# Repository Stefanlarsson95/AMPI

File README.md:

The AMPI Project
=============

##### Base on:
https://github.com/usul27/hifiberry-dsp

https://github.com/diehardsk/Volumio-OledUI

## Scrips

#### Configure DPS
Run command:
````bash
./AMPI/push_config.sh
````

#### Check voltage
Power status: 0x50005 =  bad, 0x50000 = good
````bash
sudo vcgencmd get_throttled	
````

#### RPI Core temp
The CPU core temp can be printed by the bash script:
````bash
~/AMPI/RpiTemp.sh
 ````

#### RPI AMP temp
The Amplifier heatsink temperature can med printed by the bash script:
````bash
~/AMPI/ampTemp.sh
 ````

## Instalation

#### installation steps
```bash
sudo apt update && sudo apt upgrade
sudo apt install -y python3-dev python3-pip libfreetype6-dev libjpeg-dev build-essential python3-rpi.gpio libatlas-base-dev
sudo pip3 install setuptools pip wheel
sudo pip3 install numpy
sudo pip3 install --upgrade socketIO-client3
sudo -H pip3 install --upgrade luma.oled
git clone https://github.com/Stefanlarsson95/AMPI
chmod +x ~/AMPI/AMPI.py ~/AMPI/push_config.sh ~/AMPI/RpiTemp.sh ~/AMPI/ampTemp.sh
sudo cp ~/AMPI/ampi.service /lib/systemd/system/
sudo cp ~/AMPI/dsp_config.service /lib/systemd/system/
sudo systemctl daemon-reload
sudo systemctl enable ampi.service
sudo systemctl enable dsp_config.service
```

 To enable the Oled display, SPI communication need to be enabled in the /boot/config.txt file.
 Add the following line.
 
 ```shell script
dtparam=spi=on
 ```
 
## ADAU1701 Installation
 Based on the guide and overlay from [digital-audio-labs.jimdofree.com](https://digital-audio-labs.jimdofree.com/english/raspberry-pi/adau1701-i2s-driver/)
 
 Big thanks to [MKSounds](https://github.com/MKSounds)!

Step1: Get overlay and copy to overlays folder
```bash
 git clone https://github.com/MKSounds/ADAU1701-I2S-Audio-Driver-for-Raspberry-Pi.git
```

Step2: Add overlay to overlay folder
```
sudo cp ADAU1701-I2S-Audio-Driver-for-Raspberry-Pi/adau1701-i2s.dtbo /boot/overlays
```
Step3: Add ADAU1701 to Volumio soundcards
Open soundcard JSON
```
sudo cp ADAU1701-I2S-Audio-Driver-for-Raspberry-Pi/adau1701-i2s.dtbo /boot/overlays
```
add ADAU1701 soundcard:
```
{"id":"adau1701-i2s","name":"ADAU1701 I2S Output","overlay":"adau1701-i2s","alsanum":"1","mixer":"Digital","modules":"","script":"","needsreboot":"yes"},
```
OBS: replace "Digital" with "" if Hardware volume is not used!

Step4: add dummy mixer to enable Hardware Volume

```shell script
state.Output {
	control.1 {
		iface MIXER
		name ADAU1701
		value.0 99
		value.1 99
		comment {
			access 'read write user'
			type INTEGER
			count 2
			range '0 - 99'
			tlv '00000001000000080000000000000032'
			dbmin 0
			dbmax 4950
			dbvalue.0 4950
			dbvalue.1 4950
		}
	}
}
```

 Finally reboot system
 
 ```bash
 reboot
 ```

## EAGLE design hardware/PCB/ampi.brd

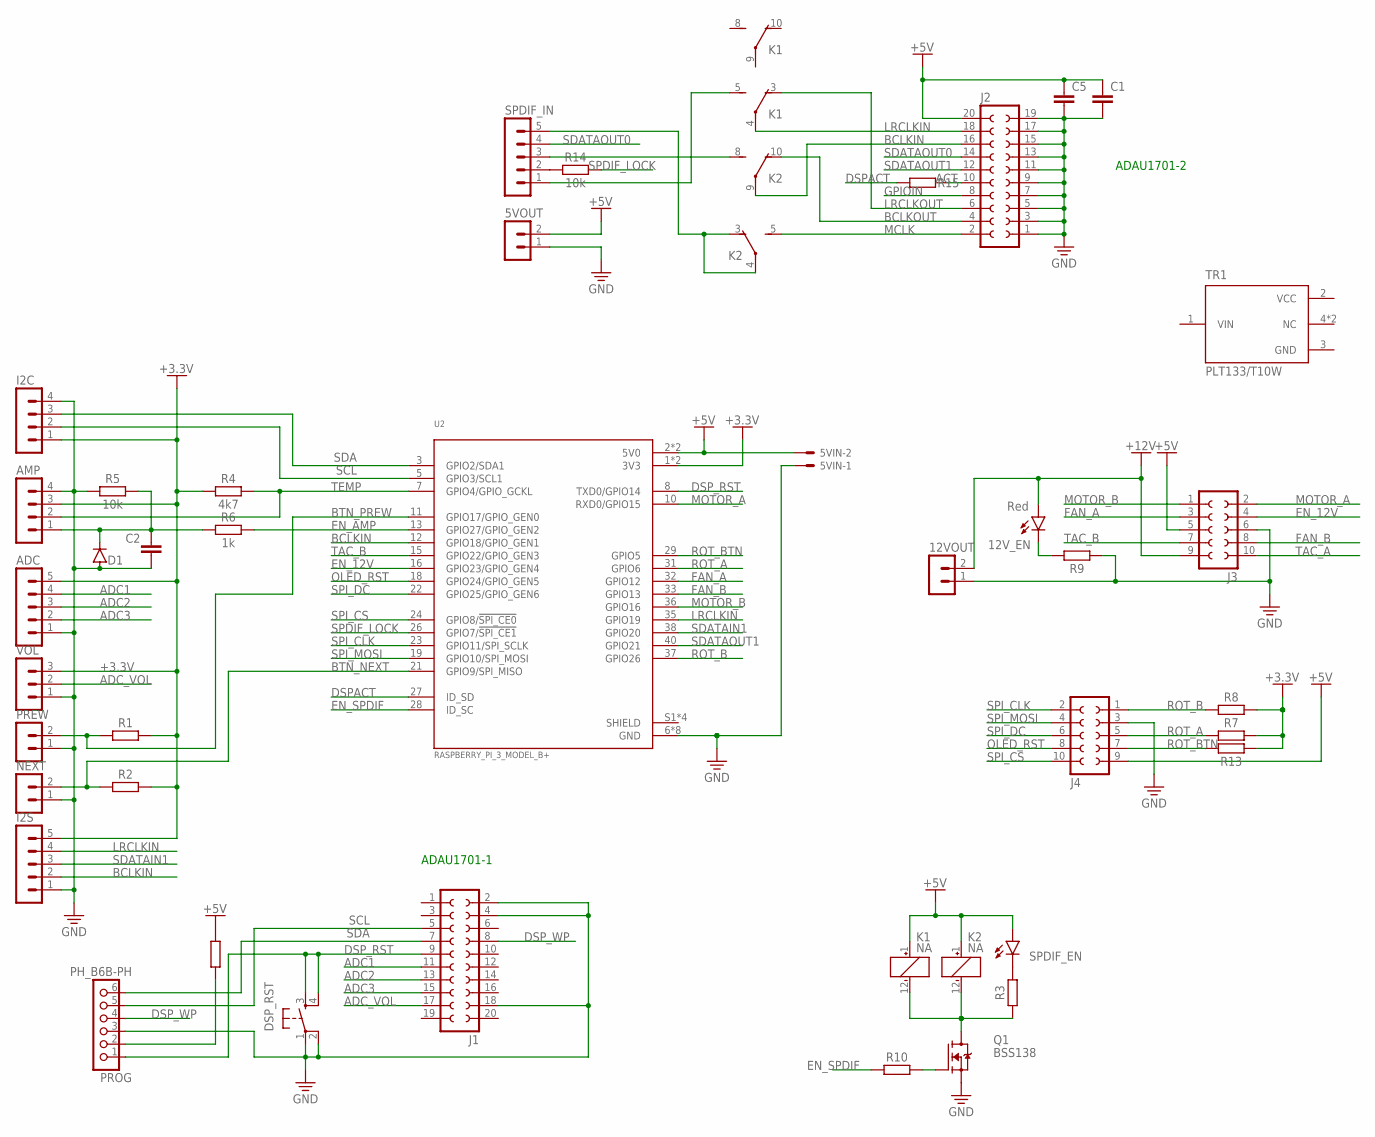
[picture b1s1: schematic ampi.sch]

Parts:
5VIN: JST-XH-02-PIN-LONG-PAD; JST-XH-02-PACKAGE-LONG-PAD
5VOUT, 12VOUT: S2B-EH
12V_EN: Red; CHIP-LED0805
ADC: S5B-EH
AMP: S4B-EH
C1: C7.5/4; C7.5B4
C2: C_CHIP-0603(1608-METRIC); CAPC1608X85
C5: C-EUC0805K; C0805K
D1: CGRM4001-G; SOD-123_MINI-SMA
DSP_RST: DTS-6
I2C: S4B-EH
I2S: S5B-EH
J1, J2: SOCKET-20V; S20V
J3, J4: SOCKET-10V; S10V
K1, K2: NA
NEXT: S2B-EH
PREW: S2B-EH
PROG: PH_B6B-PH; B6B-PH
Q1: BSS138; SOT23
R1, R2, R3, R7, R8, R9, R10, R13, R15: R_CHIP-0603(1608-METRIC); RESC1608X60
R4: 4k7; RESC1608X60
R5, R14: 10k; RESC1608X60
R6: 1k; RESC1608X60
R12: R_CHIP-0402(1005-METRIC); RESC1005X40
SPDIF_EN: LEDCHIP-LED0805; CHIP-LED0805
SPDIF_IN: S5B-EH
TR1: PLT133/T10W; XDCR_PLT133/T10W
U2: RASPBERRY_PI_3_MODEL_B+; MODULE_RASPBERRY_PI_3_MODEL_B+
VOL: S3B-EH

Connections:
+3.3V: ADC.5, AMP.3, I2C.1, I2S.5, R1.2, R2.2, R4.1, R7.2, R8.2, R13.2, U2.1 (3V3), U2.17 (3V3), VOL.3
+5V: 5VIN.2, 5VOUT.2, C1.1, C5.1, J2.20, J3.5, J4.9, K1.1 (+), K2.1 (+), R12.2, SPDIF_EN.A, U2.2 (5V0), U2.4 (5V0)
+12V: 12VOUT.2, 12V_EN.A, J3.9
ACT: J2.10, R15.2
ADC1: ADC.4, J1.11
ADC2: ADC.3, J1.13
ADC3: ADC.2, J1.15
ADC_VOL: J1.17, VOL.2
BCLKIN: I2S.2, J2.16, K2.9, U2.12 (GPIO18/GPIO_GEN1)
BCLKOUT: J2.4, K2.10 (O)
BTN_NEXT: NEXT.2, R2.1, U2.21 (GPIO9/SPI_MISO)
BTN_PREW: PREW.2, R1.1, U2.11 (GPIO17/GPIO_GEN0)
DSPACT: R15.1, U2.27 (ID_SD)
DSP_RST: DSP_RST.3, DSP_RST.4, J1.9, PROG.1, U2.8 (TXD0/GPIO14)
DSP_WP: J1.8, PROG.4
EN_12V: J3.4, U2.16 (GPIO23/GPIO_GEN4)
EN_AMP: R6.2, U2.13 (GPIO27/GPIO_GEN2)
EN_SPDIF: R10.1, U2.28 (ID_SC)
FAN_A: J3.3, U2.32 (GPIO12)
FAN_B: J3.8, U2.33 (GPIO13)
GND: 5VIN.1, 5VOUT.1, 12VOUT.1, ADC.1, AMP.4, C1.2, C2.2, C5.2, D1.A, DSP_RST.1, DSP_RST.2, I2C.4, I2S.1, J1.2, J1.4, J1.18, J2.1, J2.3, J2.5, J2.7, J2.9, J2.11, J2.13, J2.15, J2.17, J2.19, J3.6, J4.3, NEXT.1, PREW.1, PROG.3, Q1.2 (S), R5.1, R9.2, TR1.3 (GND), U2.6 (GND), U2.9 (GND), U2.14 (GND), U2.20 (GND), U2.25 (GND), U2.30 (GND), U2.34 (GND), U2.39 (GND), VOL.1
GPIOIN: J2.8
LRCLKIN: I2S.4, J2.18, K1.4, U2.35 (GPIO19)
LRCLKOUT: J2.6, K1.3 (O)
MCLK: J2.2, K2.5 (S)
MOTOR_A: J3.2, U2.10 (RXD0/GPIO15)
MOTOR_B: J3.1, U2.36 (GPIO16)
unnamed: R3.2, SPDIF_EN.C
unnamed: K1.12 (-), K2.12 (-), Q1.3 (D), R3.1
unnamed: R14.1, SPDIF_IN.2
unnamed: 12V_EN.C, R9.1
unnamed: Q1.1 (G), R10.2
unnamed: K2.8 (S), SPDIF_IN.3
unnamed: K2.3 (O), K2.4, SPDIF_IN.5
unnamed: PROG.2, R12.1
unnamed: K1.5 (S), SPDIF_IN.1
unnamed: AMP.1, C2.1, D1.C, R5.2, R6.1
OLED_RST: J4.8, U2.18 (GPIO24/GPIO_GEN5)
ROT_A: J4.5, R7.1, U2.31 (GPIO6)
ROT_B: J4.1, R8.1, U2.37 (GPIO26)
ROT_BTN: J4.7, R13.1, U2.29 (GPIO5)
SCL: I2C.2, J1.5, PROG.5, U2.5 (GPIO3/SCL1)
SDA: I2C.3, J1.7, PROG.6, U2.3 (GPIO2/SDA1)
SDATAIN1: I2S.3, U2.38 (GPIO20)
SDATAOUT0: J2.14, SPDIF_IN.4
SDATAOUT1: J2.12, U2.40 (GPIO21)
SHIELD: U2.S1 (SHIELD), U2.S2 (SHIELD), U2.S3 (SHIELD), U2.S4 (SHIELD)
SPDIF_LOCK: R14.2, U2.26 (GPIO7/!SPI_CE1!)
SPI_CLK: J4.2, U2.23 (GPIO11/SPI_SCLK)
SPI_CS: J4.10, U2.24 (GPIO8/!SPI_CE0!)
SPI_DC: J4.6, U2.22 (GPIO25/GPIO_GEN6)
SPI_MOSI: J4.4, U2.19 (GPIO10/SPI_MOSI)
TAC_A: J3.10
TAC_B: J3.7, U2.15 (GPIO22/GPIO_GEN3)
TEMP: AMP.2, R4.2, U2.7 (GPIO4/GPIO_GCKL)
VCC: TR1.2 (VCC)

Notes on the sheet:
ADAU1701-1
ADAU1701-2

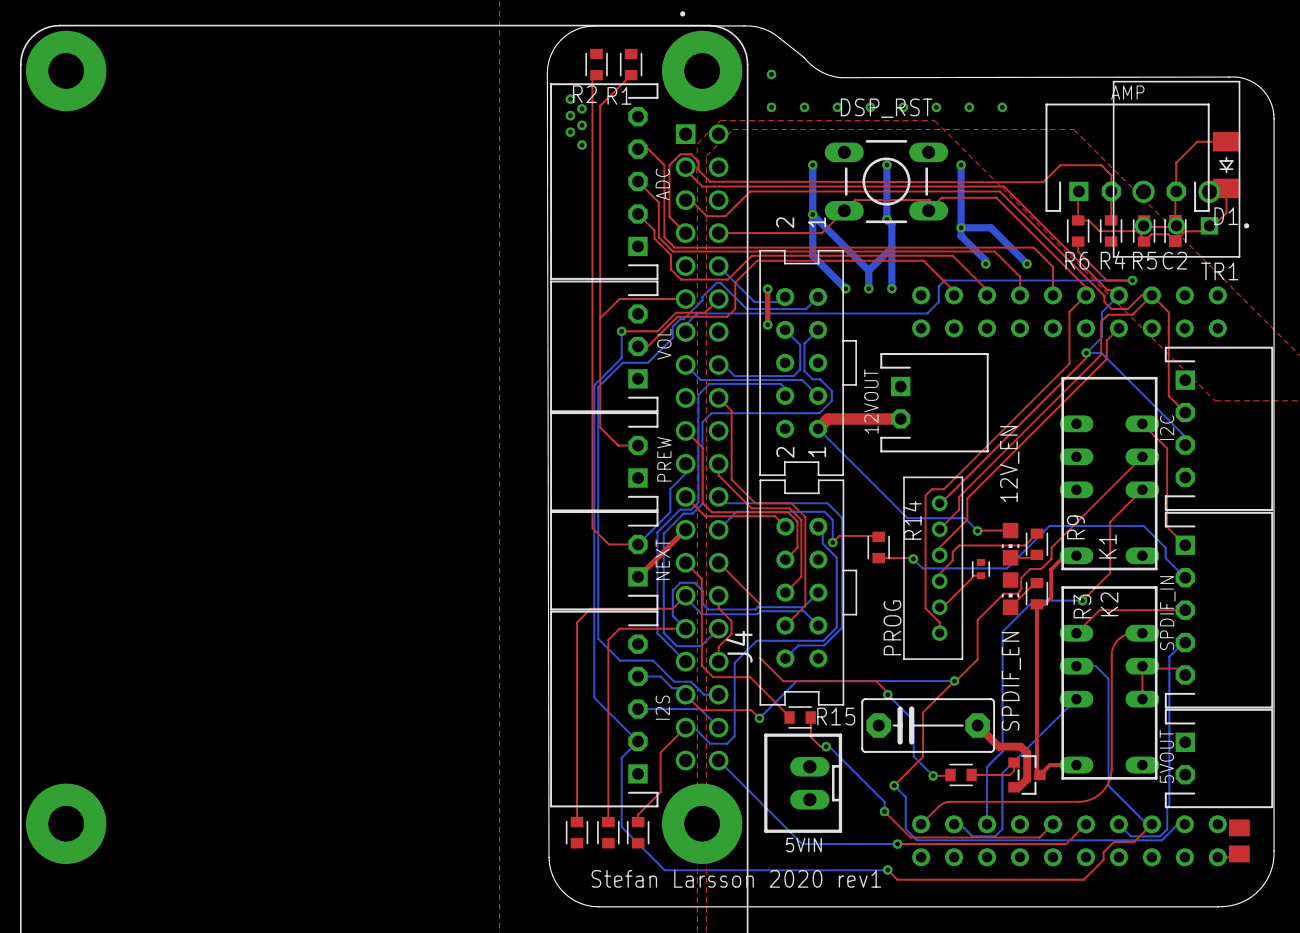
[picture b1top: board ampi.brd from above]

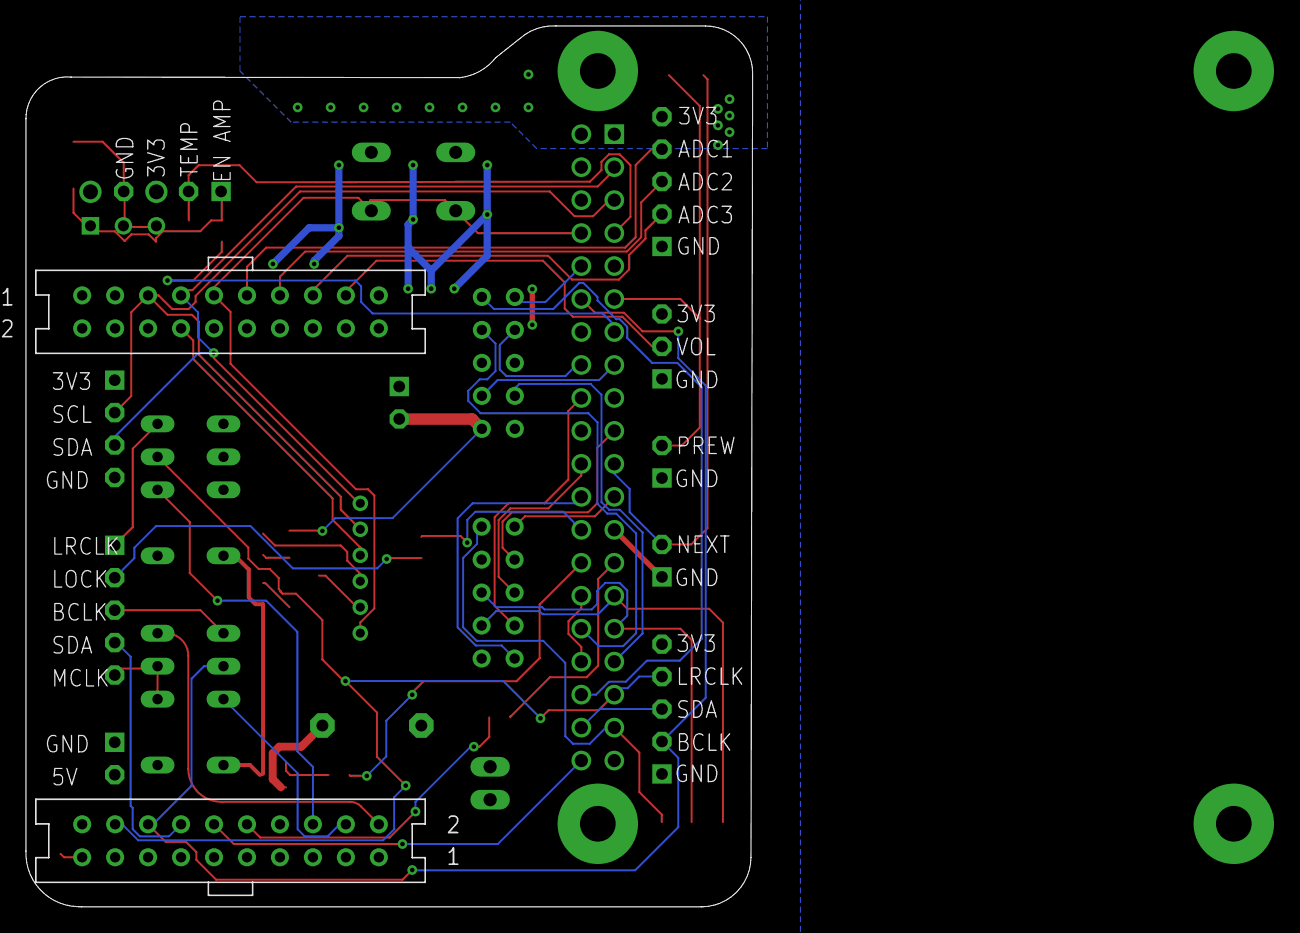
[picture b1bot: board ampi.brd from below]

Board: 2 copper layers, 56.0 x 67.9 mm, 42 parts (2 on the bottom side), 53 nets.

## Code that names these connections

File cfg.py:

import RPi.GPIO as GPIO
import modules.dsp_register as dsp_reg
import pathlib
from luma.core.interface.serial import spi
from luma.oled.device import ssd1322
from modules.logger import *
from hardware import sigmaimporter
from threading import Lock, Event

# Setup
log = Log()
_path = str(pathlib.Path().absolute())
_root_path = _path.rsplit('/', 1)[0]
i2c_lock = Lock()
volume_event = Event()  # todo implement or remove
eq_event = Event()  # todo implement or remove

"""
General
"""
amp_always_off = False
emit_volume = False
emit_track = False
emit_shutdown = False
standby = False
mute = False
log.set_level(LOGLEVEL.INFO)

"""
Temp control
"""
AMP_TEMP_TARGET = 60
CPU_TEMP_TARGET = 60
CHASSIS_FAN_MAX_RPM = 5000
AMP_FAN_MAX_RPM = 4500

"""
Sources
"""
RPI_ENABLED = True
AUX_ENABLED = True
SPDIF_ENABLED = False
SOURCE_AUX = 0
SOURCE_RPI = 1
SOURCE_SPDIF = 2
SOURCE_AUTO = 3
INIT_SOURCE = None  # will read default from DSP
volumio_source = INIT_SOURCE

"""
GPIO config
"""
# Setup Mutual action pins
# pwr12v = POWER12V()

# Input
ACTIVITY_PIN = 0
ROT_ENTER_PIN = 5
ROT_A_PIN = 6
SPDIF_LOCK_PIN = 7
BTN_PREV = 17
BTN_NEXT = 9
AMPLIFIER_FAN_TACH_PIN = None
CHASSIS_FAN_TACH_PIN = 22
ROT_B_PIN = IR_PIN = 26
LRCLK_PIN = 19

# Output
SPDIF_ENABLE_PIN = 1
DSP_RST_PIN = 14
VOL_UP_PIN = 15
VOL_DN_PIN = 16
CHASSIS_FAN_PIN = 12
AMPLIFIER_FAN_PIN = 13
PWR_EN_12V_PIN = 23
AMP_EN_PIN = 27

"""
OlED/UI
"""
VOLUMIO_HOST = volumio_host = 'localhost'
VOLUMIO_PORT = volumio_port = 3000
VOLUME_DT = 5  # volume adjustment step

UPDATE_INTERVAL = 1 / 15  # 1/fps
STANDBY_UPDATE_INTERVAL = 1
PIXEL_SHIFT_TIME = 120  # time between picture position shifts in sec.

# todo merge to state class usage
STATE_NONE = -1
STATE_PLAYER = 0
STATE_PLAYLIST_MENU = 1
STATE_QUEUE_MENU = 2
STATE_VOLUME = 3
STATE_SHOW_INFO = 4
STATE_LIBRARY_MENU = 5
STATE_CLOCK = 6


class STATE:
    NONE = -1
    PLAYER = 0
    PLAYLIST_MENU = 1
    QUEUE = 2
    VOLUME = 3
    INFO_MENU = 4
    LIBRARY_MENU = 5
    CLOCK = 6
    EQ = 7
    EQ_MENU = 8
    SOURCE_MENU = 9


# todo move to oled cfg to not initiate for all cfg imports
interface = spi(device=0, port=0)
oled = ssd1322(interface)

oled.WIDTH = 256
oled.HEIGHT = 64
oled.state = STATE_NONE
oled.state_default = STATE_CLOCK
oled.stateTimeout = 0
oled.update_interval = UPDATE_INTERVAL
oled.timeOutRunning = True
oled.activeSong = 'AMPI'
oled.activeArtist = 'VOLUMIO'
oled.playState = 'unknown'
oled.playPosition = 0
oled.ptime = 0
oled.pstart = 0
oled.duration = 0
oled.modal = None
oled.playlistoptions = []
oled.queue = []
oled.libraryFull = []
oled.libraryNames = []
oled.volume = 0
oled.volumeControlDisabled = False
oled.standby = False

"""
Sigma studio registers 
"""

_dsp_reg_adr = dsp_reg.get_reg(xml_path='/home/volumio/AMPI/SigmaStudio/AMPI_1.xml')

VOLUME_READ_REG = _dsp_reg_adr.get('master_volume.vol_redback')
AUX_DETECT_REG = _dsp_reg_adr.get('source_select.aux_signal_detect')
RPI_DETECT_REG = _dsp_reg_adr.get('source_select.rpi_signal_detect')
SPDIF_DETECT_REG = _dsp_reg_adr.get('source_select.spdif_signal_detect')
DSP_SOURCE_SELECT = _dsp_reg_adr.get('source_select.Input_selector')
CORE_REG = 0x081C
MUTE_BIT_MASK = 0b0010

"""
DSP conf
"""
DSP_DATA = sigmaimporter.read_txbuffer('/home/volumio/AMPI/SigmaStudio/TxBuffer_IC_1.dat')
DSP_SAMPLE_FREQ_LIM = 5

if __name__ == '__main__':
    print(_dsp_reg_adr)

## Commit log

2019-01-13 init commit
2019-02-10 new Main
2019-02-10 cleanup
2019-04-27 LocalChanges: init commit
2019-04-27 cleanup
    cleanup
    cleanup
    cleanup
    cleanup
    cleanup
    cleanup
2019-04-28 Hardware: included daughterboard i/o
2019-05-11 PINOUT: fix
2019-05-14 SigmaTcp: added SigmaStudio TCP support
2019-05-21 README: added amp temp comands
2019-05-23 added startup script
2019-05-29 init volumio port
2019-06-04 Pinout: update
2019-06-09 implemented readback from readbackCell
2019-06-09 initial commit Volume
2019-06-09 initial merge OledUi
2019-06-10 volume: implemented set_hw_volume()
2019-06-11 ampi: fixed startup service and volume
2019-07-19 v2: initial commit
2019-08-02 v2: cleanup file tree
2019-08-02 misc: compressed drivers
2019-08-10 ampi: changed log levels
2019-08-10 Display: fix image path
2019-08-10 logger: syntax cleanup
2019-08-18 gitignore: remove settings ignore
2019-08-18 ampi.service path fix
2019-09-16 CASE_DSP: added CASE Sigmaproject
2019-10-14 FanControll: first implementation
2019-10-18 Volume: read guard added, Hardware: Pushconfig eeprom
2019-10-19 div fixes
2019-10-20 impl pot controll loundess
2019-11-09 volume: read frequense limeting
2019-12-13 bugfix and resource management
2019-12-13 fix Screen classes
2020-04-27 initial merge towards python3
2020-05-06 installation instructions migrated to python3
2020-07-27 fix DSP radback error. initial working SPDIF implementation
2020-07-31 update DSP program, fix volume module and init implementation of input_select, SPDIF
2020-08-03 included startup melody
2020-08-03 dsp_register xml parser
2020-08-03 implemented dps_reggister parser
2020-08-04 fix signal detetction and path to param xml
2020-08-04 updated ADAU1701 install guide for HW volume
2020-08-13 init activety detect readig
2020-08-15 added responce_parser
2020-08-28 fixi GPIO setup bug and imp REW reading to SigmaStudio parser
2020-09-06 minor fixes
2020-09-06 included .idea files
2020-09-06 fix Rotary encoder PINs
2020-09-06 fix mute amp on init
2020-09-06 implemented DSP init on startup
2020-09-06 fix input selector hierarchy select
2020-09-06 moved functions to ampi_backend
2020-09-06 fix standby mode
2020-09-06 fix update interval
2020-09-06 fix volume activety callback
2020-09-08 volume modul updated
2020-09-13 fix input_selector
2020-09-13 working sw volume change
2020-09-20 initial temp_controller code
2020-09-23 working temp and volume controller
2020-10-17 add temp controller
2020-10-29 add pcb files
2020-11-20 fix pinout and temp_controller test
2020-11-21 fix input selector and temp controller
2020-11-21 initial remote code
2020-11-22 final v3, release
2020-11-22 initial v4
2020-11-22 fix volume control
2020-11-25 adding 12v mutual control module
2020-11-25 fix power module
2020-11-25 adding amplifier control module
2020-11-25 fix temp controller
2020-12-05 working ampi
2020-12-11 fix volumio volume event bug
2020-12-21 minor bugfixes
2020-12-28 temp_controller update
2020-12-28 volume class update to VOLUME2
